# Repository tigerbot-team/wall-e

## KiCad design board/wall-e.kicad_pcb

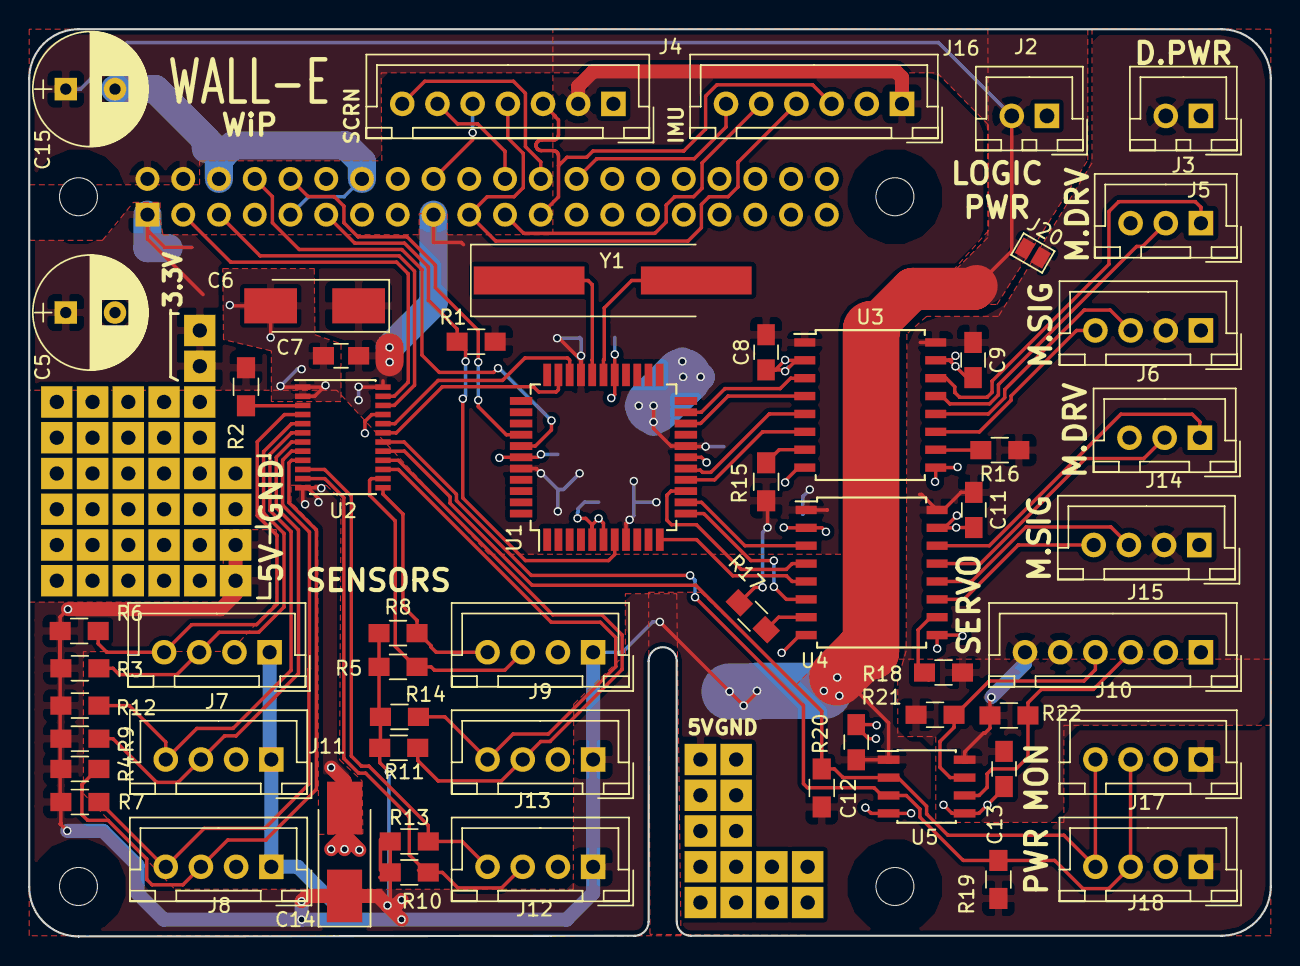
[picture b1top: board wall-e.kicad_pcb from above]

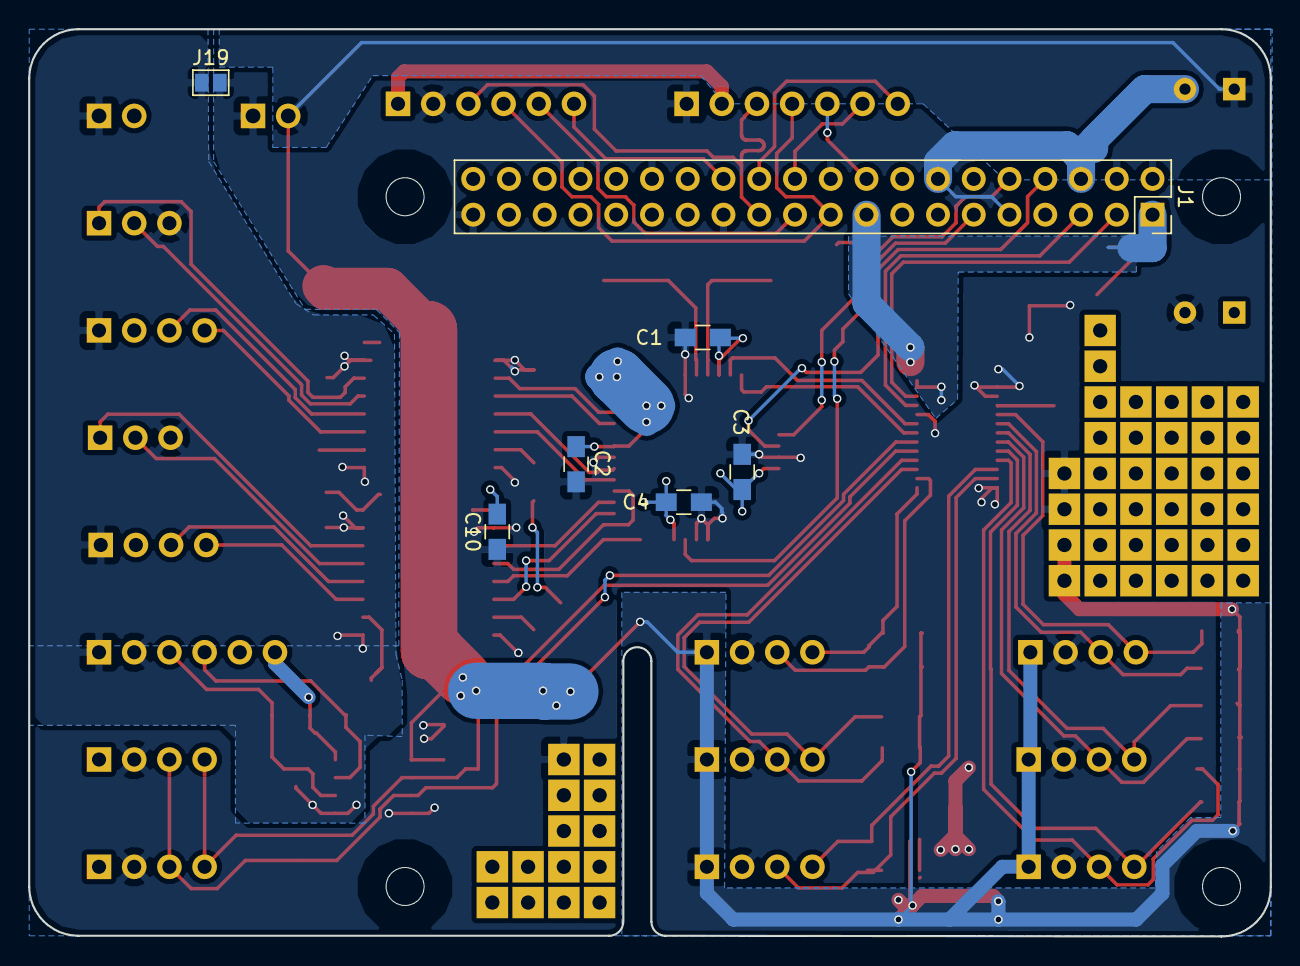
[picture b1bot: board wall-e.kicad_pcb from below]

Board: 2 copper layers, 88.2 x 64.4 mm, 63 parts (7 on the bottom side), 58 nets.

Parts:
C1, C2, C3, C4, C12, C13: 0.1u; C_0805_HandSoldering
C5, C15: 470u; CP_Radial_D8.0mm_P3.50mm
C6, C14: 10u; CP_Tantalum_Case-C_EIA-6032-28_Hand
C7, C8, C9, C10, C11: 0u1; C_0805_HandSoldering
J1: Raspberry_Pi_2_3; Socket_Strip_Straight_2x20_Pitch2.54mm
J2: LogicPwr; JST_XH_B02B-XH-A_02x2.50mm_Straight
J3: NoisyPwr; JST_XH_B02B-XH-A_02x2.50mm_Straight
J4: SSD1351; JST_XH_B07B-XH-A_07x2.50mm_Straight
J5: MotorDrv1; JST_XH_B03B-XH-A_03x2.50mm_Straight
J6: Motor1; JST_XH_B04B-XH-A_04x2.50mm_Straight
J7, J8, J9, J11, J12, J13: VL53L0X; JST_XH_B04B-XH-A_04x2.50mm_Straight
J10: PCA9685; JST_XH_B06B-XH-A_06x2.50mm_Straight
J14: MotorDrv2; JST_XH_B03B-XH-A_03x2.50mm_Straight
J15: Motor2; JST_XH_B04B-XH-A_04x2.50mm_Straight
J16: IMU; JST_XH_B06B-XH-A_06x2.50mm_Straight
J17, J18: INA219; JST_XH_B04B-XH-A_04x2.50mm_Straight
J19, J20: GS2
R1, R2: 10k; R_0805_HandSoldering
R3, R4, R5, R6, R7, R8, R9, R10, R11, R12, R13, R14, R15, R16, R17, R18, R19, R20: 4k7; R_0805_HandSoldering
R21, R22: 1k5; R_0805_HandSoldering
U1: P8X32A-Q44; LQFP-44_10x10mm_Pitch0.8mm
U2: TCA9548A_TSSOP; TSSOP-24_4.4x7.8mm_Pitch0.65mm
U3, U4: ISO7742; SOIC-16W_7.5x10.3mm_Pitch1.27mm
U5: ISO1541; SOIC-8_3.9x4.9mm_Pitch1.27mm
Y1: Crystal; Crystal_SMD_HC49-SD_HandSoldering

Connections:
+3V3: C1.1, C2.1, C3.1, C4.1, C5.1, C6.1, C7.1, C8.2, C10.2, J1.1, J1.17, J4.2, J16.1, R1.1, R2.2, R15.2, R17.2, U1.8, U1.18, U1.30, U1.40, U2.24, U3.1, U4.1
+5V: C12.1, C14.1, C15.1, J1.2, J1.4, J2.2, J7.1, J8.1, J9.1, J11.1, J12.1, J13.1, J17.1, J18.1, J20.1, R3.1, R4.1, R5.1, R6.1, R7.1, R8.1, R9.1, R10.1, R11.1, R12.1, R13.1, R14.1, R19.1, R20.1, U5.1
+5VP: C9.1, C11.1, C13.1, J3.2, J6.2, J10.5, J10.6, J15.2, J20.2, R16.1, R18.1, R21.1, R22.1, U3.16, U4.16, U5.8
GND: C1.2, C2.2, C3.2, C4.2, C5.2, C6.2, C7.2, C8.1, C10.1, C12.2, C14.2, C15.2, J1.6, J1.9, J1.14, J1.20, J1.25, J1.30, J1.34, J1.39, J2.1, J4.1, J7.2, J8.2, J9.2, J11.2, J12.2, J13.2, J16.2, J17.2, J18.2, J19.2, U1.5, U1.6, U1.17, U1.27, U1.39, U2.1, U2.2, U2.12, U2.21, U3.2, U3.8, U4.2, U4.8, U5.4
GNDA: C9.2, C11.2, C13.2, J3.1, J5.3, J6.1, J10.1, J10.2, J14.3, J15.1, J19.1, U3.9, U3.15, U4.9, U4.15, U5.5
I2C_ISO_SCL: J10.3, R22.2, U5.6
I2C_ISO_SDA: J10.4, R21.2, U5.7
I2C_M0_SCLK: J7.3, R3.2, U2.5
I2C_M0_SDA: J7.4, R6.2, U2.4
I2C_M1_SCLK: J11.3, R9.2, U2.7
I2C_M1_SDA: J11.4, R12.2, U2.6
I2C_M2_SCLK: J8.3, R4.2, U2.9
I2C_M2_SDA: J8.4, R7.2, U2.8
I2C_M3_SCLK: J12.3, R10.2, U2.11
I2C_M3_SDA: J12.4, R13.2, U2.10
I2C_M4_SCLK: J9.3, R5.2, U2.14
I2C_M4_SDA: J9.4, R8.2, U2.13
I2C_M5_SCLK: J13.3, R11.2, U2.16
I2C_M5_SDA: J13.4, R14.2, U2.15
I2C_M6_SCLK: J17.3, J18.3, R19.2, U2.18, U5.3
I2C_M6_SDA: J17.4, J18.4, R20.2, U2.17, U5.2
I2C_M7_SCLK: U1.31, U2.20
I2C_M7_SDA: U1.32, U2.19
M2_DIR: U1.13, U4.3
M2_ENCA: U1.11, U4.5
M2_ENCB: U1.12, U4.6
M2_PWM: U1.14, U4.4
M3_DIR: U1.21, U3.3
M3_ENCA: U1.16, U3.5
M3_ENCB: U1.15, U3.6
M3_PWM: U1.20, U3.4
unnamed: J5.1, U3.14
unnamed: J5.2, U3.13
unnamed: J6.3, U3.12
unnamed: J6.4, U3.11
unnamed: J14.1, U4.14
unnamed: J14.2, U4.13
unnamed: J15.3, U4.12
unnamed: J15.4, U4.11
unnamed: R2.1, U2.3
unnamed: R15.1, U3.7
unnamed: R16.2, U3.10
unnamed: R17.1, U4.7
unnamed: R18.2, U4.10
unnamed: U1.28, Y1.2
unnamed: U1.29, Y1.1
PI_I2C_SCLK: J1.5, U2.22
PI_I2C_SDA: J1.3, U2.23
PI_RX: J1.10, U1.37
PI_SPI_CE0: J1.24, J4.7
PI_SPI_CE1: J1.26, J16.6
PI_SPI_MISO: J1.21, J16.5
PI_SPI_MOSI: J1.19, J4.4, J16.4
PI_SPI_SCLK: J1.23, J4.3, J16.3
PI_TX: J1.8, U1.38
PROP_RES: J1.11, R1.2, U1.7
SCREEN_DC: J1.22, J4.6
SCREEN_RST: J1.18, J4.5

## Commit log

2018-08-03 WiP on board.
2018-08-12 Add IMU and power sensors.
2018-10-07 Commit libraries and clean up.
2018-10-07 Start to group components on board.
2018-11-07 Do some routing
2018-11-09 More routing; add Pi outline.
2018-11-09 Pi outline
2018-11-12 Smaller board
2018-11-12 Routed
2018-11-19 Tweaks
2018-11-19 Add keepouts around screws
2018-11-19 Fix DRC errors
2018-11-28 Swap in through-hole cap
2018-12-01 Move board over ports and re-route.
2018-12-01 Update silkscreen
2018-12-01 Tweaks: add cap and fill.
2018-12-01 Fix position of R1 label.
2018-12-01 Round corners.
2018-12-02 ADd prototyping area.
2018-12-02 Tweaks.
2018-12-02 Move power monitors onto logic power.
2018-12-02 More proto area.
2018-12-03 Add 5V cap and tweak.
2018-12-04 Add bridge between 5V rails.
2018-12-06 Tweak mux layout.
2018-12-07 Added pour round vias
2018-12-09 v1.0
2018-12-23 Connect IMU to SPI0, add pour to mux ground.
2019-03-03 Add sound clips
